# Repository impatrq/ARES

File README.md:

<div align="center">

<br/>
<br/>

<p align="center">

</p>

<p align="center">

</p>

</div>

## 📖 Documentación del Proyecto

Toda la documentación técnica y de seguimiento del sistema se encuentra centralizada en el directorio `/docs`.

* **Carpeta de Campo** `/docs/carpeta_de_campo/`: Contiene el registro iterativo del proyecto en formato `.pdf`. Documenta detalladamente el progreso semanal, las decisiones tomadas y el aporte técnico individual de cada integrante a lo largo del ciclo de desarrollo anual.
  
<div>&nbsp;</div>

## 🛠 Componentes Utilizados

* **Microcontrolador (ESP32-S3):** 
  * Ejecuta el firmware principal. Mantiene la transmisión de datos sin pérdida de paquetes bajo conexión Wi-Fi estable. Actualmente falta optimizar el modo Deep Sleep para mejorar la eficiencia energética.

* **Filtro Analógico / Sensor ECG (AD8232):** 
  * El acondicionamiento de la señal base es correcto, pero se requiere ajustar los filtros pasivos por hardware para reducir el ruido inducido por el movimiento del usuario.

* **Conversor Analógico-Digital (ADS1115):** 
  * Resuelve la falta de linealidad del ADC interno del ESP32. Aporta conversión de 16 bits, garantizando la resolución necesaria para interpretar la señal cardíaca del AD8232 sin distorsiones digitales.

* **Módulo de Carga (TP4056):** 
  * Gestiona la carga y protección de la batería de litio, asegurando la alimentación autónoma y segura del circuito completo.

> [!NOTE] 
> - Las imágenes y descripciones detalladas de cada elemento se encuentran en `/hardware/componentes/` 
> - Las hojas de datos de referencia se ubican en `/docs/datasheets/`

<div>&nbsp;</div>

## 🌟 Sobre el Proyecto

**ARES** (*Arrhythmia Real-time Evaluation System*) es un sistema IoT diseñado para el monitoreo electrocardiográfico continuo, que busca reemplazar cirugías invasivas. 

<table>
  <tr>
    <td style="text-align: center;">
      
      <p style="font-style: italic; font-size: 14px; margin-top: 5px;">protoboard</p>
    </td>    
    <td style="text-align: center;">
      
      <p style="font-style: italic; font-size: 14px; margin-top: 5px;">placa tht</p>
    </td>
    </td>    
    <td style="text-align: center;">
      
      <p style="font-style: italic; font-size: 14px; margin-top: 5px;">placa final</p>
    </td>
  </tr>
</table>

<div>&nbsp;</div>

## 🎯 Características Principales

* **Adquisición Analógica-Digital:** Captura de ECG de un canal mediante un *front-end* analógico (AD8232) con filtrado activo. La digitalización se delega a un ADC de 16 bits (ADS1115), garantizando una resolución precisa y eliminando el ruido inherente al conversor interno del microcontrolador.

* **Procesamiento y Telemetría:** Un ESP32-S3 orquesta el muestreo estricto de los datos y ejecuta la transmisión continua e ininterrumpida de paquetes vía Wi-Fi, manteniendo una latencia optimizada hacia la nube.

* **Gestión Energética:** El PCB cuenta con un circuito de carga y protección basado en el TP4056, diseñado para operar con baterías de litio y asegurar la autonomía del sistema durante las pruebas físicas.

* **Integración Ergonomica:** Circuito 100% componentes SMD embebido en un top deportivo de compresión. Utiliza electrodos textiles para mantener el contacto con la piel, eliminando adhesivos médicos y fricción mecánica.

* **Seguimiento Web en Tiempo Real:** Los paquetes telemétricos son recibidos por un *dashboard* remoto  que procesa los datos, ofreciendo una interfaz responsiva para la evaluación inmediata.

<div>&nbsp;</div>

## 🤝 Contacto

Para desarrollo, auditoría de hardware o consultas de inversión:

Mail - proyectoares26@gmail.com

Link del Proyecto: [https://github.com/impatrq/ARES](https://github.com/impatrq/ARES)

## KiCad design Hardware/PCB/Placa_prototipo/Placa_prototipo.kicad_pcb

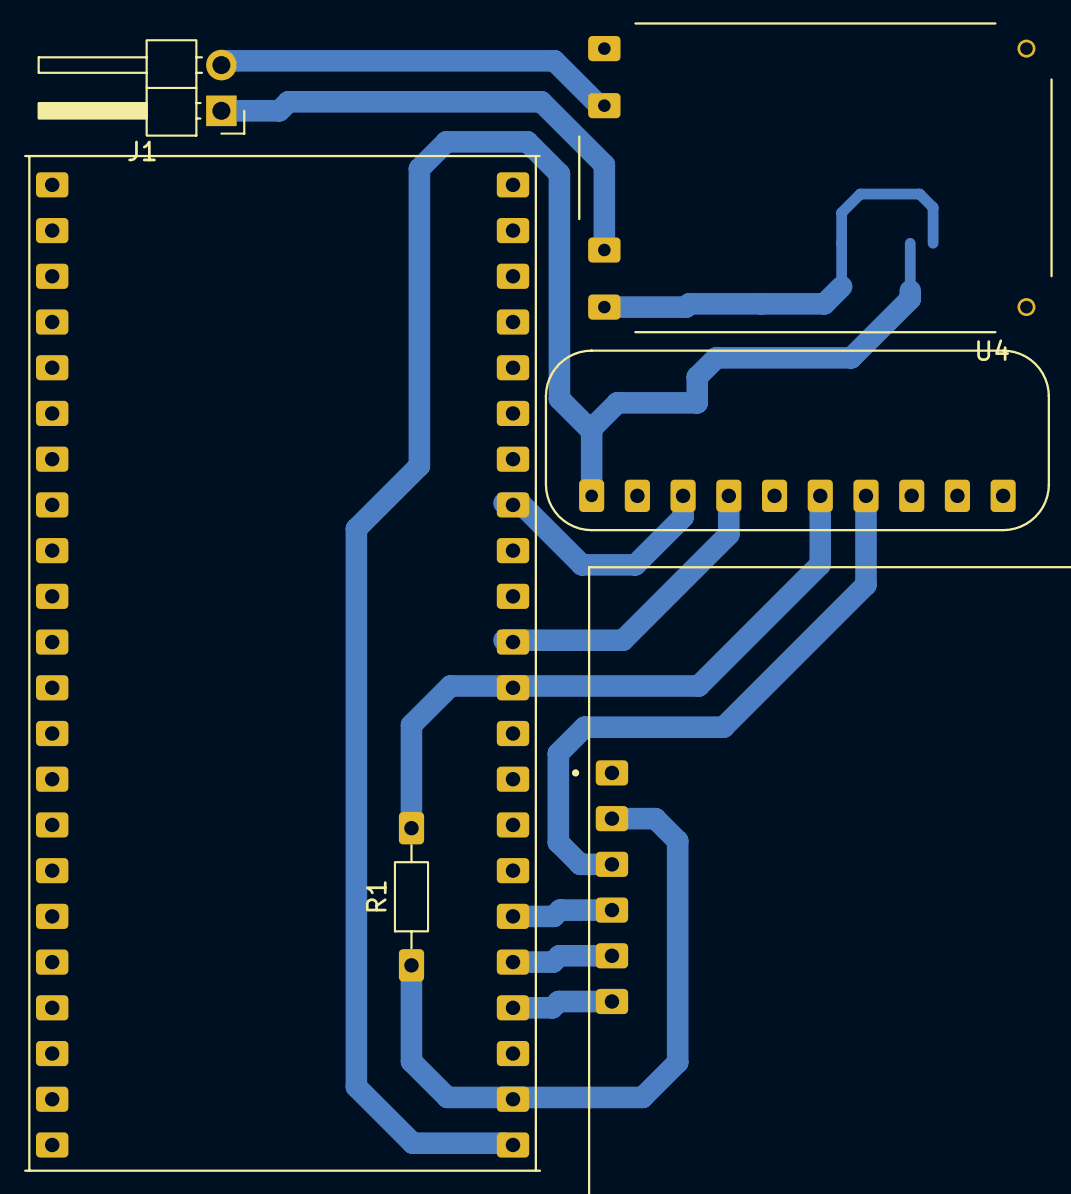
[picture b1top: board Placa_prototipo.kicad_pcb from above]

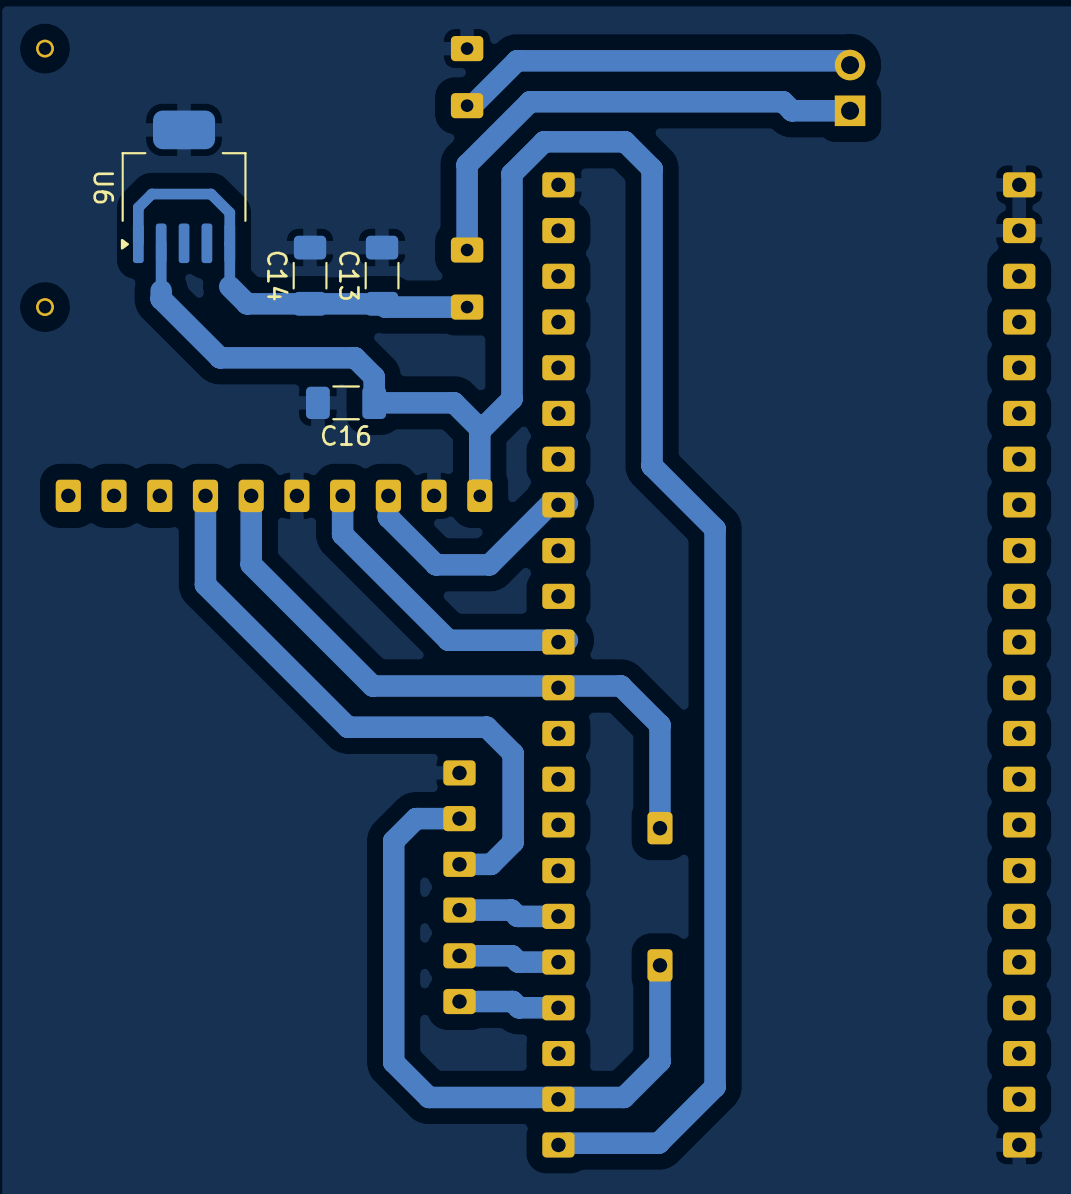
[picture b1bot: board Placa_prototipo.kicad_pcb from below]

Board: 2 copper layers, 10 parts (4 on the bottom side), 12 nets.

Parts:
C13, C16: 10µF; C_1206_3216Metric_Pad1.33x1.80mm_HandSolder
C14: 100nF; C_1206_3216Metric_Pad1.33x1.80mm_HandSolder
J1: Conn_01x02_Pin; PinHeader_1x02_P2.54mm_Horizontal
R1: 10k; R_Axial_DIN0204_L3.6mm_D1.6mm_P7.62mm_Horizontal
U1: ESP32-S3-DEVKITC-1-N32R8V; XCVR_ESP32-S3-DEVKITC-1-N32R8V
U2: AD8232; MODULE_SEN-12650
U3: ADS1115; MODULE_ZC261500
U4: TP4056_MICRO-USB_CHARGER_-_1A; MODULE_TP4056_MICRO-USB_CHARGER_-_1A
U6: TPS73733DCQ; SOT-223-6_TabPin3

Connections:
+3.3V: C16.1, R1.1, U1.J1_1 (3V3), U1.J1_2 (3V3), U2.JP3_2 (3.3V), U3.10 (VDD), U6.2 (OUT)
+BATT: C13.1, C14.1, U4.OUT_P (OUT+), U6.1 (IN), U6.5 (EN)
GND: C13.2, C14.2, C16.2, U1.J1_22 (GND), U1.J3_1 (GND), U1.J3_21 (GND), U1.J3_22 (GND), U2.JP3_1 (GND), U3.6 (ADDR), U3.9 (GND), U4.OUT_N (OUT-), U6.3 (GND-1)
unnamed: J1.1, U4.BAT_P (BAT+)
unnamed: J1.2, U4.BAT_N (BAT-)
unnamed: U1.J1_4 (GPIO4), U2.JP3_6 (SDN)
unnamed: U1.J1_5 (GPIO5), U2.JP3_5 (LO+)
unnamed: U1.J1_6 (GPIO6), U2.JP3_4 (LO-)
unnamed: U1.J1_12 (GPIO8), U3.7 (SDA)
unnamed: U1.J1_15 (GPIO9), U3.8 (SCL)
unnamed: R1.2, U1.J1_11 (GPIO18), U3.5 (ALERT)
unnamed: U2.JP3_3 (SIGNAL_OUT), U3.4 (A0)

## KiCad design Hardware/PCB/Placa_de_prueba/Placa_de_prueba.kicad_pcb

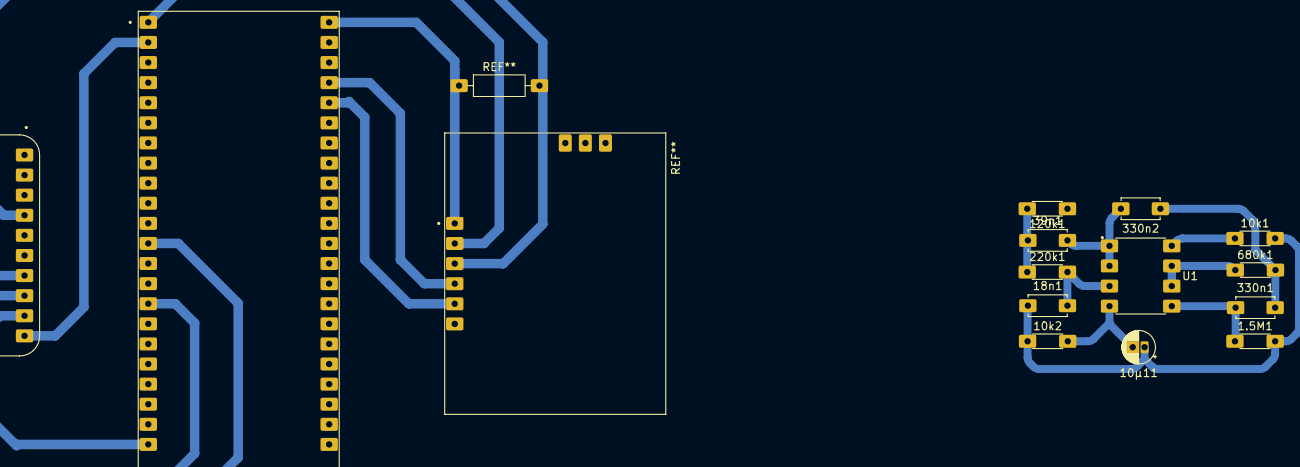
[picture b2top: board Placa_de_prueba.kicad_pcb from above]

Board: 2 copper layers, 12 parts (0 on the bottom side), 9 nets.

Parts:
1.5M1, 10k1, 10k2, 120k1, 220k1, 680k1: R; R_Axial_DIN0204_L3.6mm_D1.6mm_P5.08mm_Horizontal
10µ11: C; CP_Radial_D4.0mm_P1.50mm
18n1, 39n1, 330n1, 330n2: C; C_Disc_D4.7mm_W2.5mm_P5.00mm
U1: MCP6002-I_P; DIP787W46P254L927H533Q8

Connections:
3.3v: 10k1.1, U1.8 (VDD)
A: 1.5M1.2, 10k1.2, 10k2.1, 10µ11.1, 18n1.1
GND: 10k2.2, 10µ11.2, U1.4 (VSS)
unnamed: 39n1.1, 120k1.2, 220k1.1
unnamed: 330n1.2, 330n2.1, 680k1.2
unnamed: 18n1.2, 220k1.2, U1.3 (VINA+)
unnamed: 39n1.2, 330n2.2, U1.1 (VOUTA), U1.2 (VINA-)
unnamed: 1.5M1.1, 330n1.1, U1.5 (VINB+)
unnamed: 680k1.1, U1.6 (VINB-), U1.7 (VOUTB)

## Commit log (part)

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2026-04-08 cargo el antreproyecto al repositorio
2026-04-16 Create Docs
2026-04-17 Agregar carpeta del anteproyecto
2026-06-10 Feat: Agrego simulacion de filtros
2026-06-10 Feat: Imagen del circuito
